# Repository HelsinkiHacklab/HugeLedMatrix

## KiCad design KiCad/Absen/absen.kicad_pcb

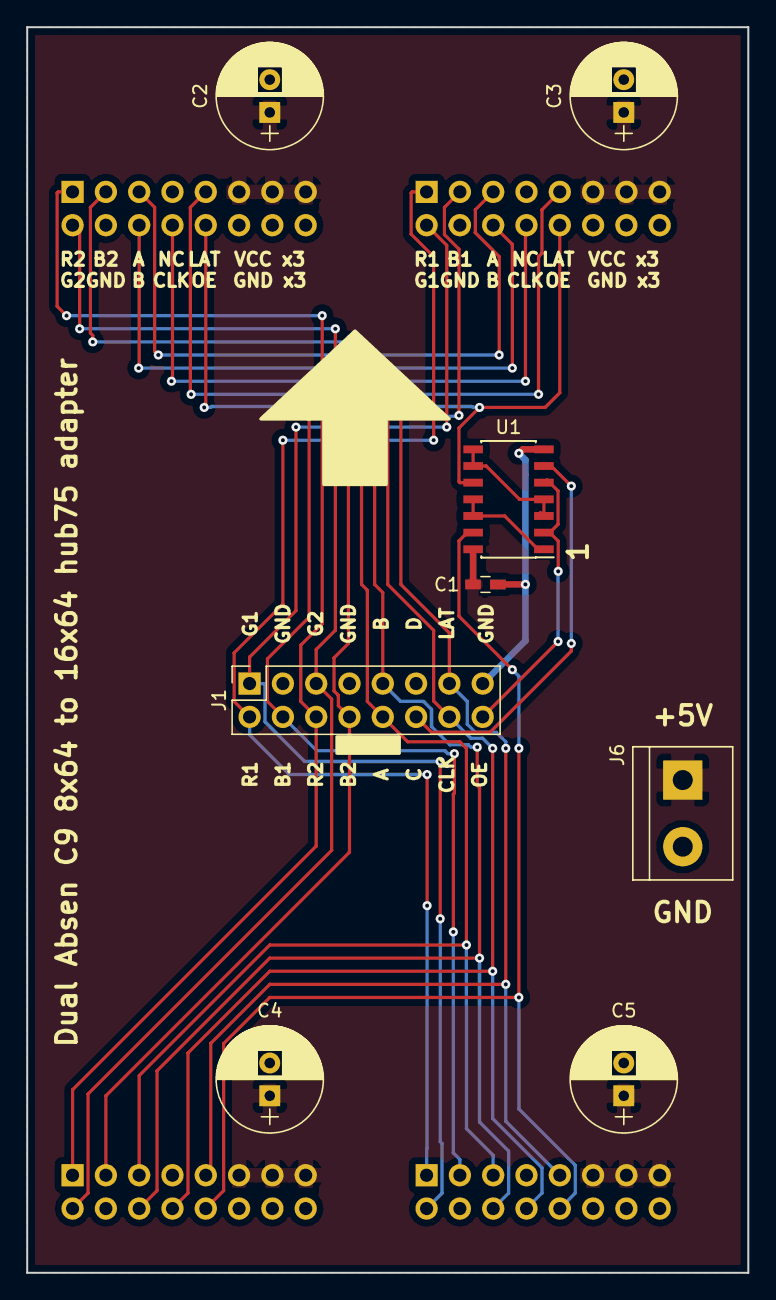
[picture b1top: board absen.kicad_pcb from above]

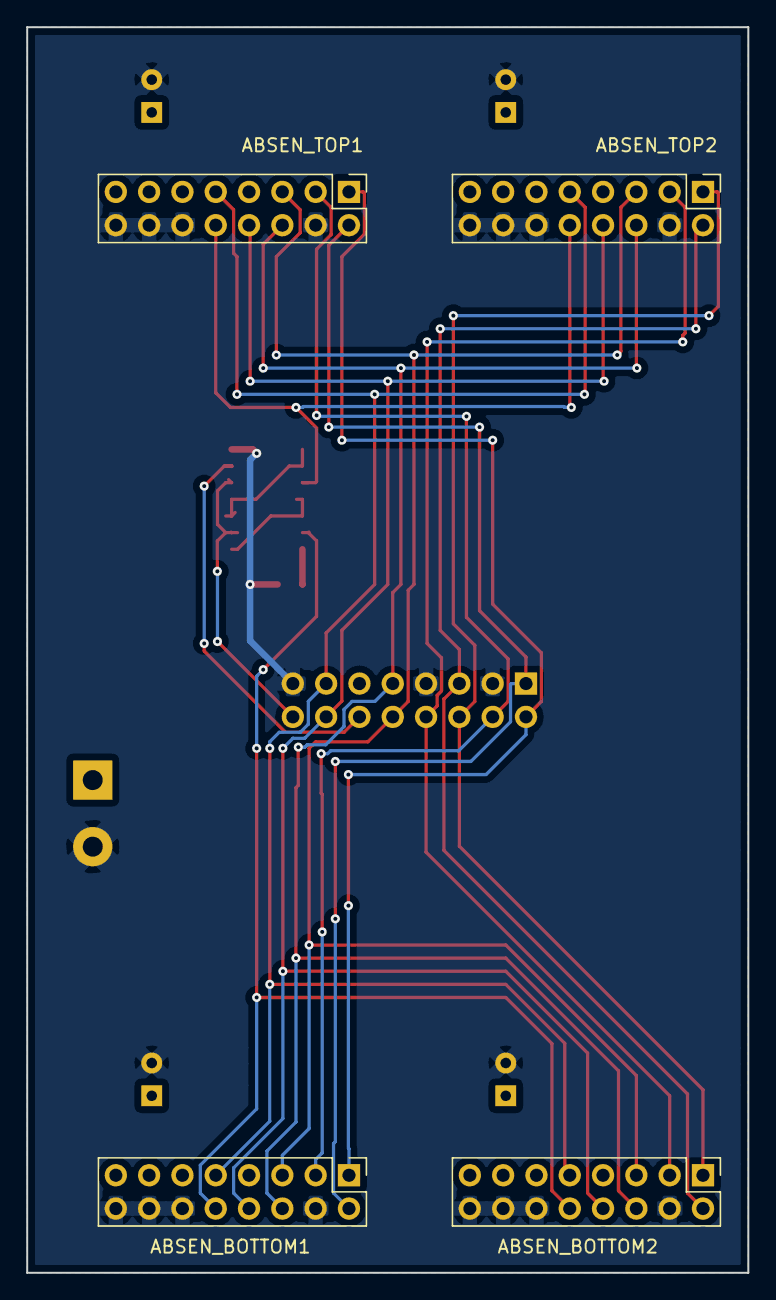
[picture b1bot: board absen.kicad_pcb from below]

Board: 2 copper layers, 55.0 x 95.0 mm, 12 parts (4 on the bottom side), 18 nets.

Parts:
ABSEN_BOTTOM1, ABSEN_BOTTOM2: ABSEN_OUT; Pin_Header_Straight_2x08_Pitch2.54mm
ABSEN_TOP1, ABSEN_TOP2: ABSEN_OUT; Pin_Header_Straight_2x08_Pitch2.54mm
C1: 100n; C_0603_HandSoldering
C2, C3, C4, C5: CP_Radial_D8.0mm_P2.50mm
J1: HUB75_IN; Socket_Strip_Straight_2x08_Pitch2.54mm
J6: PWR IN; TerminalBlock_bornier-2_P5.08mm
U1: 7402; SOIC-14_3.9x8.7mm_Pitch1.27mm

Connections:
+5V: ABSEN_BOTTOM1.11, ABSEN_BOTTOM1.13, ABSEN_BOTTOM1.15, ABSEN_BOTTOM2.11, ABSEN_BOTTOM2.13, ABSEN_BOTTOM2.15, ABSEN_TOP1.11, ABSEN_TOP1.13, ABSEN_TOP1.15, ABSEN_TOP2.11, ABSEN_TOP2.13, ABSEN_TOP2.15, C1.1, C2.1, C3.1, C4.1, C5.1, J6.1, U1.14
/!OE1: U1.3, U1.4, U1.8, U1.9
/!OE2: U1.1, U1.11, U1.12
/A: ABSEN_BOTTOM1.5, ABSEN_BOTTOM2.5, ABSEN_TOP1.5, ABSEN_TOP2.5, J1.10
/B: ABSEN_BOTTOM1.6, ABSEN_BOTTOM2.6, ABSEN_TOP1.6, ABSEN_TOP2.6, J1.9
/B1: ABSEN_BOTTOM1.3, ABSEN_TOP1.3, J1.4
/B2: ABSEN_BOTTOM2.3, ABSEN_TOP2.3, J1.8
/C: J1.12, U1.6
/CLK: ABSEN_BOTTOM1.8, ABSEN_BOTTOM2.8, ABSEN_TOP1.8, ABSEN_TOP2.8, J1.14
/G1: ABSEN_BOTTOM1.2, ABSEN_TOP1.2, J1.1
/G2: ABSEN_BOTTOM2.2, ABSEN_TOP2.2, J1.5
/LATCH: ABSEN_BOTTOM1.9, ABSEN_BOTTOM2.9, ABSEN_TOP1.9, ABSEN_TOP2.9, J1.13
/OE: J1.16, U1.2, U1.5
/OE1: ABSEN_TOP1.10, ABSEN_TOP2.10, U1.10
/OE2: ABSEN_BOTTOM1.10, ABSEN_BOTTOM2.10, U1.13
/R1: ABSEN_BOTTOM1.1, ABSEN_TOP1.1, J1.2
/R2: ABSEN_BOTTOM2.1, ABSEN_TOP2.1, J1.6
GND: ABSEN_BOTTOM1.4, ABSEN_BOTTOM1.12, ABSEN_BOTTOM1.14, ABSEN_BOTTOM1.16, ABSEN_BOTTOM2.4, ABSEN_BOTTOM2.12, ABSEN_BOTTOM2.14, ABSEN_BOTTOM2.16, ABSEN_TOP1.4, ABSEN_TOP1.12, ABSEN_TOP1.14, ABSEN_TOP1.16, ABSEN_TOP2.4, ABSEN_TOP2.12, ABSEN_TOP2.14, ABSEN_TOP2.16, C1.2, C2.2, C3.2, C4.2, C5.2, J1.3, J1.7, J1.15, J6.2, U1.7

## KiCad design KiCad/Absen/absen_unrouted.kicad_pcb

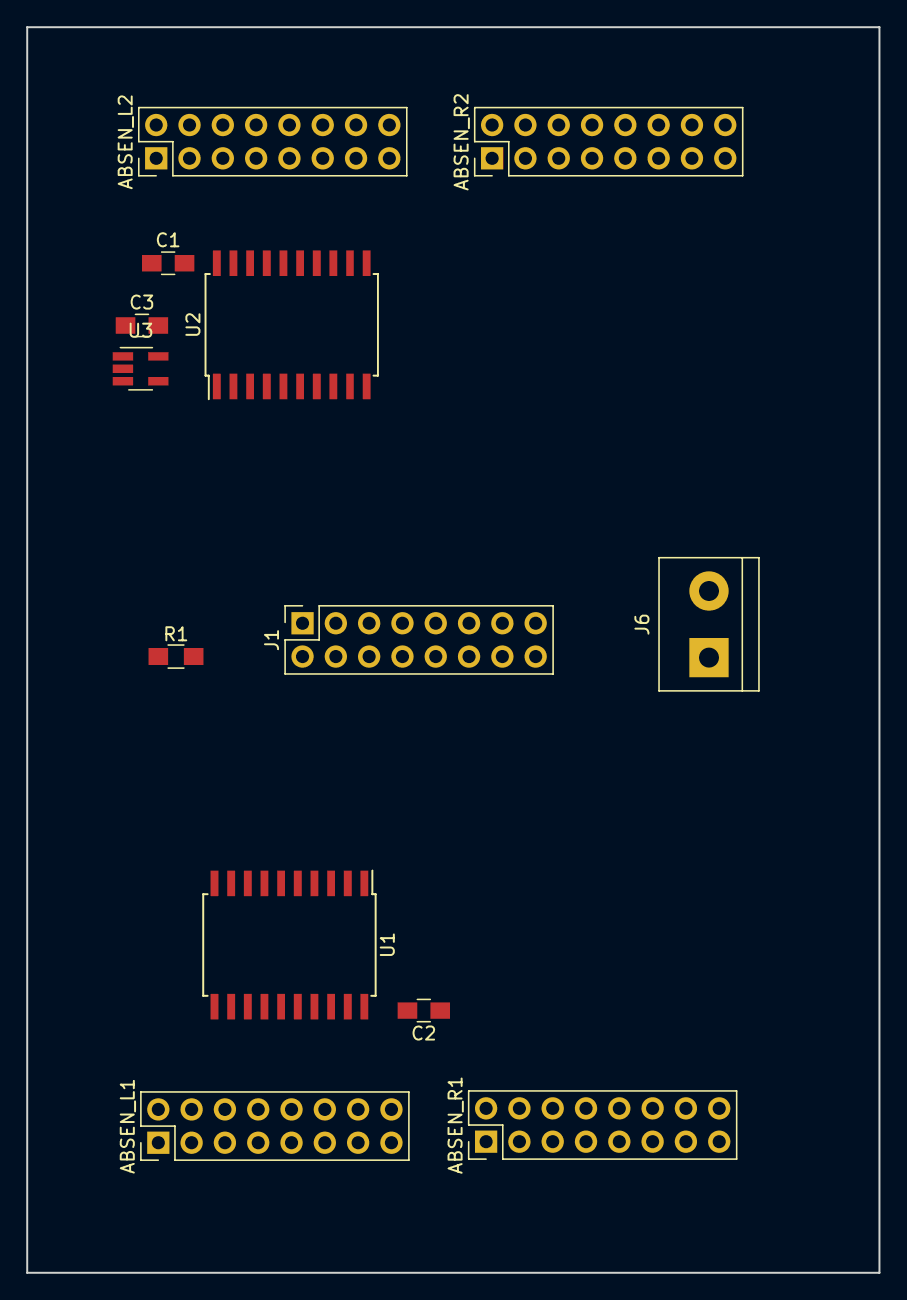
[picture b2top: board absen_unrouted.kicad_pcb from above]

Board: 2 copper layers, 65.0 x 95.0 mm, 13 parts (0 on the bottom side), 22 nets.

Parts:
ABSEN_L1, ABSEN_L2: ABSEN_OUT; Pin_Header_Straight_2x08_Pitch2.54mm
ABSEN_R1, ABSEN_R2: ABSEN_OUT; Pin_Header_Straight_2x08_Pitch2.54mm
C1, C2, C3: 100n; C_0805_HandSoldering
J1: HUB75_IN; Socket_Strip_Straight_2x08_Pitch2.54mm
J6: PWR IN; TerminalBlock_bornier-2_P5.08mm
R1: 10k; R_0805_HandSoldering
U1, U2: 74HC245; SOIC-20W_7.5x12.8mm_Pitch1.27mm
U3: 74AHC1G04; SOT-23-5_HandSoldering

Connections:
+5V: ABSEN_L1.11, ABSEN_L1.13, ABSEN_L1.15, ABSEN_L2.11, ABSEN_L2.13, ABSEN_L2.15, ABSEN_R1.11, ABSEN_R1.13, ABSEN_R1.15, ABSEN_R2.11, ABSEN_R2.13, ABSEN_R2.15, C1.2, C2.2, C3.2, J6.1, U1.20, U2.20, U3.5
/A: ABSEN_L1.5, ABSEN_L2.5, ABSEN_R1.5, ABSEN_R2.5, J1.10
/B: ABSEN_L1.6, ABSEN_L2.6, ABSEN_R1.6, ABSEN_R2.6, J1.9
/B1: ABSEN_L1.3, ABSEN_L2.3, J1.4
/B2: ABSEN_R1.3, ABSEN_R2.3, J1.8
/C: J1.12, U1.19, U3.2
/CLK: J1.14, U1.2, U2.2
/CLK1: ABSEN_L1.8, ABSEN_R1.8, U1.18
/CLK2: ABSEN_L2.8, ABSEN_R2.8, U2.18
/G1: ABSEN_L1.2, ABSEN_L2.2, J1.1
/G2: ABSEN_R1.2, ABSEN_R2.2, J1.5
/LATCH: J1.13, U1.3, U2.3
/LATCH1: ABSEN_L1.9, ABSEN_R1.9, U1.17
/LATCH2: ABSEN_L2.9, ABSEN_R2.9, U2.17
/LOW: R1.1, U1.1, U2.1
/OE: J1.16, U1.4, U2.4
/OE1: ABSEN_L1.10, ABSEN_R1.10, U1.16
/OE2: ABSEN_L2.10, ABSEN_R2.10, U2.16
/R1: ABSEN_L1.1, ABSEN_L2.1, J1.2
/R2: ABSEN_R1.1, ABSEN_R2.1, J1.6
GND: ABSEN_L1.4, ABSEN_L1.12, ABSEN_L1.14, ABSEN_L1.16, ABSEN_L2.4, ABSEN_L2.12, ABSEN_L2.14, ABSEN_L2.16, ABSEN_R1.4, ABSEN_R1.12, ABSEN_R1.14, ABSEN_R1.16, ABSEN_R2.4, ABSEN_R2.12, ABSEN_R2.14, ABSEN_R2.16, C1.1, C2.1, C3.1, J1.3, J1.7, J1.15, J6.2, R1.2, U1.10, U2.10, U3.3
unnamed: U2.19, U3.4

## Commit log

2018-04-18 KiCad files for the adapter pcb
2018-04-18 Pixel mapping code
2018-04-18 Better readme
